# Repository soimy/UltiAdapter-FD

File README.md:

# UltiAdapter-FD
Ultimaker's UltiController Adapter for RAMPS-FD

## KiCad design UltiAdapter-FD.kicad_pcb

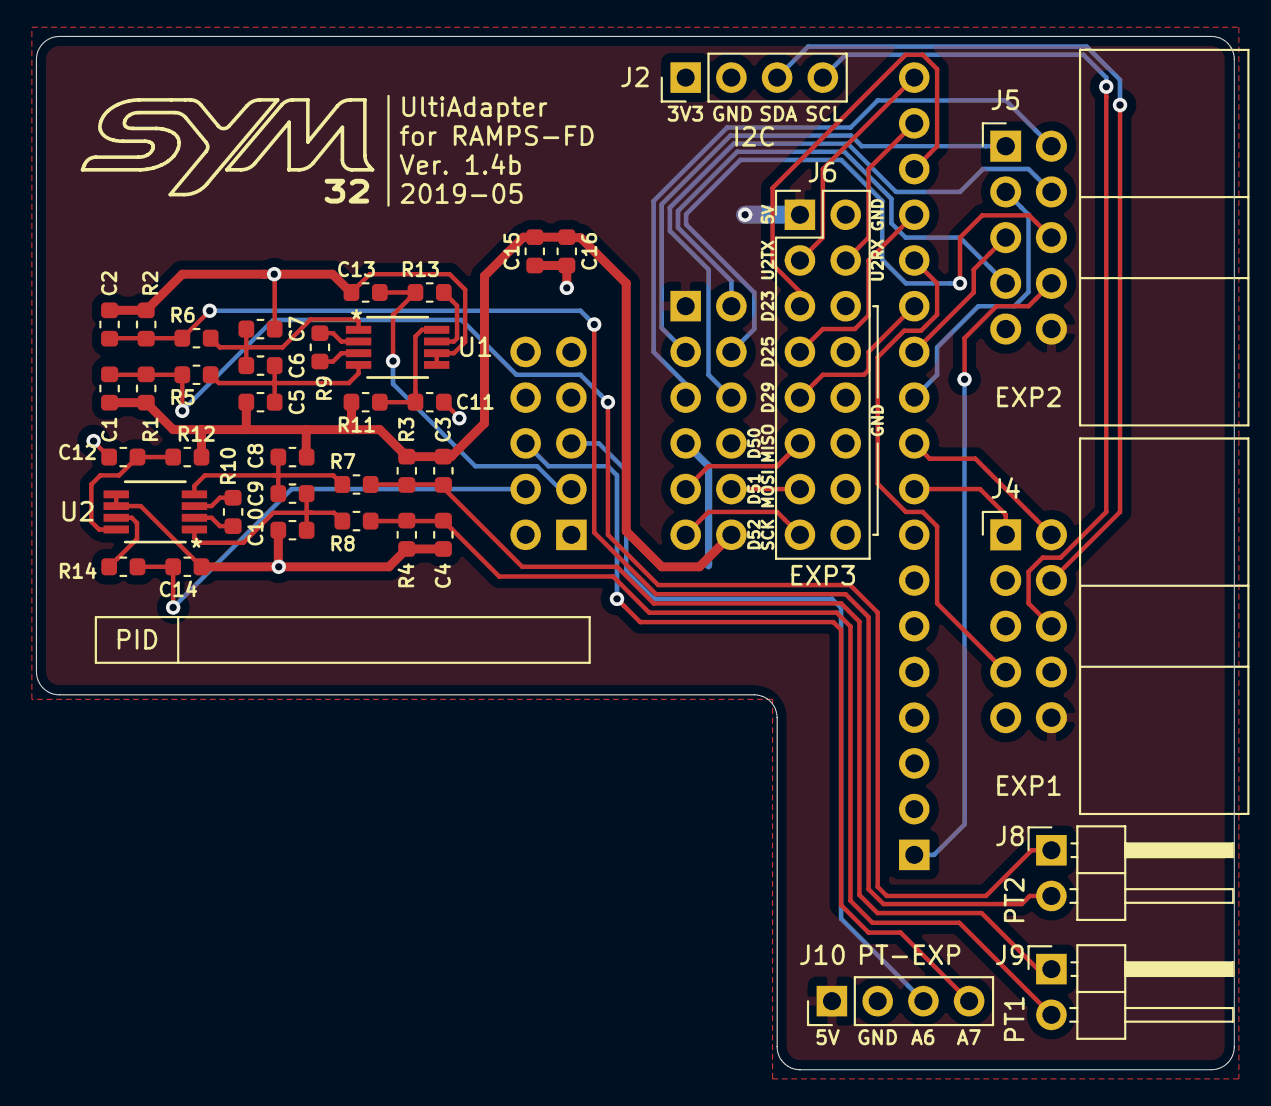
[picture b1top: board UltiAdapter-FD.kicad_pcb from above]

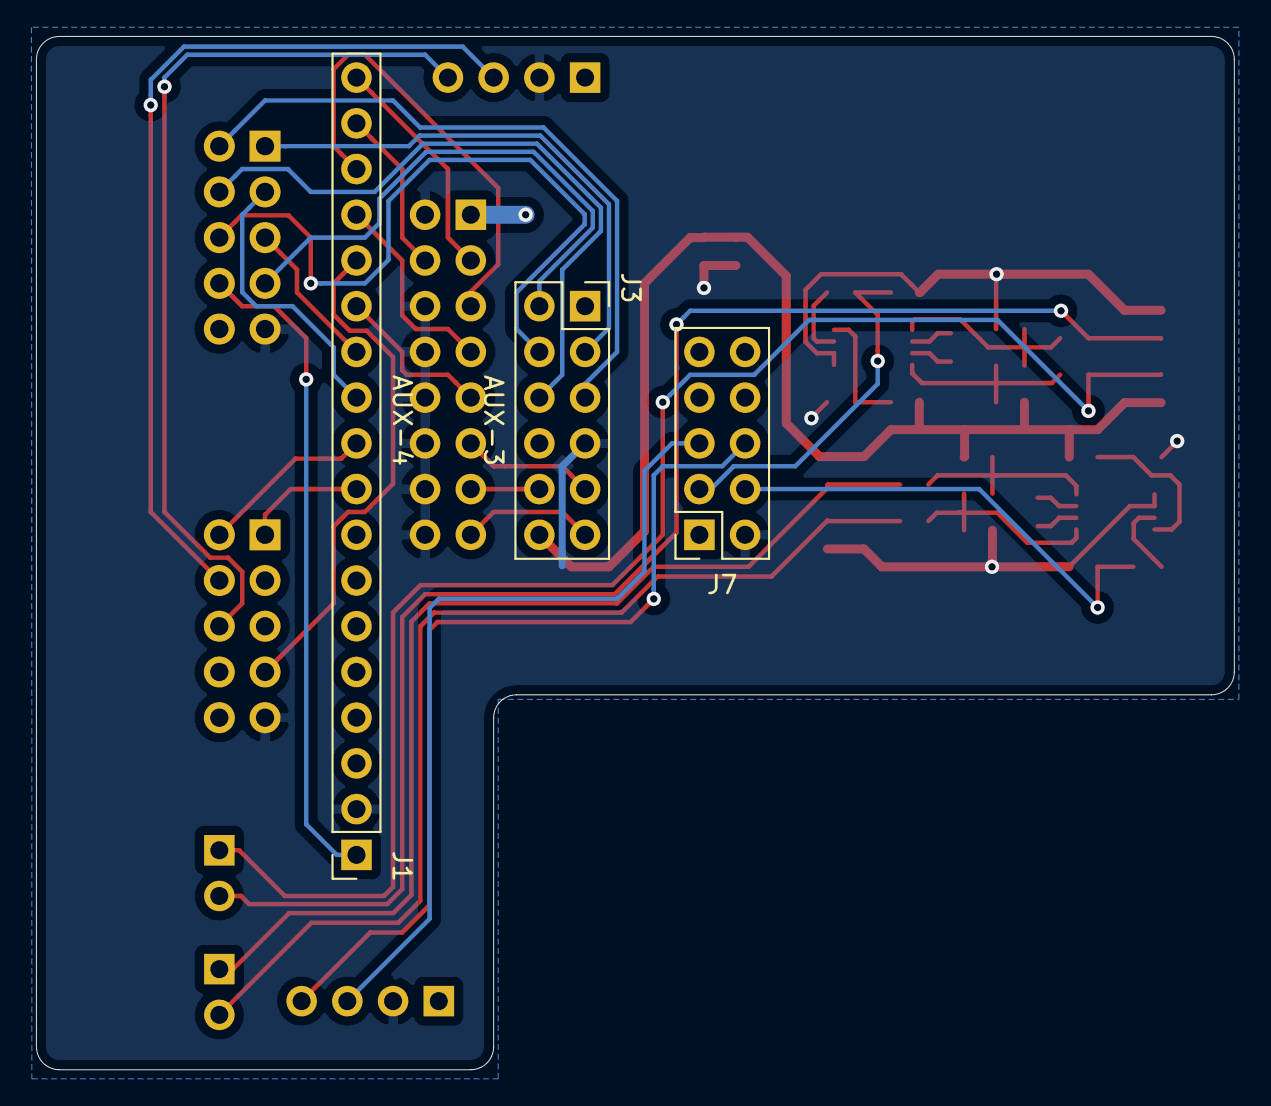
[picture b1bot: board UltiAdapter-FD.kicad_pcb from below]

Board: 2 copper layers, 66.5 x 57.4 mm, 42 parts (3 on the bottom side), 43 nets.

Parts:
C1, C2, C3, C4, C5, C7, C8, C10, C11, C12, C16: 100nF; C_0603_1608Metric
C6, C9: 1uF; C_0603_1608Metric
C13, C14: 10nF; C_0603_1608Metric
C15: 10uF; C_0603_1608Metric
J1: AUX-4; PinSocket_1x18_P2.54mm_Vertical
J2: I2C; PinHeader_1x04_P2.54mm_Vertical
J3: AUX-3; PinSocket_2x06_P2.54mm_Vertical
J4: EXP1; IDC-Header_2x05_P2.54mm_Horizontal
J5: EXP2; IDC-Header_2x05_P2.54mm_Horizontal
J6: EXP3; PinHeader_2x08_P2.54mm_Vertical
J7: AUX-2; PinSocket_2x05_P2.54mm_Vertical
J8: RTD01; PinHeader_1x02_P2.54mm_Horizontal
J9: RTD02; PinHeader_1x02_P2.54mm_Horizontal
J10: PT-EXP; PinHeader_1x04_P2.54mm_Vertical
R1, R2, R3, R4: 2K2; R_0603_1608Metric
R5, R6, R7, R8: 10K; R_0603_1608Metric
R9, R10: 5k49; R_0603_1608Metric
R11, R12, R13, R14: 100R; R_0603_1608Metric
U1, U2: INA826AIDGKR; DGK8

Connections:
+3V3: C1.1, C3.1, C5.1, C8.1, C15.1, C16.1, J1.1, J2.1, J3.12, J5.8, R1.2, R3.2, R11.2, R12.2
+5V: J3.1, J4.10, J5.10, J6.1, J10.1
A4-RTD01: C13.1, J7.3, R13.1
A5-RTD02: C14.1, J7.4, R14.1
A6-RTD03: J7.5, J10.3
A7-RTD04: J7.6, J10.4
D23: J1.16, J6.5
D25: J1.15, J6.7
D27-LCD_RESET: J1.14, J4.7
D29: J1.13, J6.9
D31-BTN_EN2: J1.12, J5.5
D33-BTN_EN1: J1.11, J5.3
D35-BTN_ENC: J1.10, J4.2
D37-BEEP_PIN: J1.9, J4.1
D49-SD_DETECT: J3.2, J5.7
D50-MISO: J3.9, J6.11
D51-MOSI: J3.10, J6.13
D52-SCK: J3.11, J6.15
GND: C2.2, C4.2, C7.2, C10.2, C11.2, C12.2, C13.2, C14.2, C15.2, C16.2, J1.2, J2.2, J3.7, J4.9, J5.9, J6.2, J6.6, J6.8, J6.10, J6.12, J6.14, J6.16, J7.2, J10.2, R2.1, R4.1, U1.5, U1.6, U2.5, U2.6
MISO: J3.3, J5.1
MOSI: J3.4, J5.6
unnamed: C1.2, J8.1, R1.1, R5.2
unnamed: C2.1, J8.2, R2.2, R6.2
unnamed: C3.2, J9.1, R3.1, R7.2
unnamed: C4.1, J9.2, R4.2, R8.2
unnamed: C5.2, C6.1, R5.1, U1.4
unnamed: C6.2, C7.1, R6.1, U1.1
unnamed: C8.2, C9.1, R7.1, U2.4
unnamed: C9.2, C10.1, R8.1, U2.1
unnamed: C11.1, R11.1, U1.8
unnamed: C12.1, R12.1, U2.8
unnamed: R9.1, U1.2
unnamed: R9.2, U1.3
unnamed: R10.1, U2.2
unnamed: R10.2, U2.3
unnamed: R13.2, U1.7
unnamed: R14.2, U2.7
SCK: J3.5, J5.2
SCL: J2.4, J4.6
SDA: J2.3, J4.4
SPI_CS1: J3.6, J5.4
UART2_RX: J1.17, J6.4
UART2_TX: J1.18, J6.3

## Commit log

2019-04-15 Initial upload
2019-04-15 Add INA82AIDGKR library
    PT100 sensor input WIP
2019-04-16 Re-organize file name & structures
2019-04-17 PT100 Sensor WIP2
2019-04-17 Add PT100 Amplifies x2
2019-04-17 Renaming media files
2019-04-18 Add PT expansion port & Power anti-noise
2019-04-19 Fix short circuit on AUX-4
    Turns out I mis-placed +V_LOGIC and GND on AUX-4 lead to board short
2019-04-19 Reverse EXP1 & EXP2 pin order
2019-04-19 Re-route pcb on Reversed EXP1 & EXP2 pin
2019-04-23 Little routing tweak
2019-04-23 Change PT100 Amplifier input voltage to 3V3
2019-04-23 Silk screen pin comment
2019-05-03 Bug fix: Wrong pin 1&4 of INA826 Amplifier
    Fixed Schematic and rerouted.
2019-05-03 Bump verison to 1.4b
2021-02-25 Update 1.4b pcb

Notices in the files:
parts and their libraries:
Copyright 2016 Accelerated Designs. All rights reserved.
